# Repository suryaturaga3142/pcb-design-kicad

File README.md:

# pcb-design-kicad
Designing PCBs is an integral skill that takes you beyond breadboarding and using dev boards. It lets you combine different components with very little latency, and makes products look awesome!

Here's a collection of some of my favorite PCBs that I really enjoyed designing on my own. I don't just go and draw stuff up. I think of a use case first, like connecting devices to my laptop or using AUX cables for STM32. Then I go about employing the skills available to me.

## flash_adc1

My own design of a flash ADC that makes use of less digital combinationl logic and more buffering and chaining of comparators to directly obtain the converted reading. It's a unique design that saves on resources by leveraging a binary search style of output.

Typical ADCs are either SAR (Successive Approximation Register), Sigma-Delta, or Flash. SAR is resource efficient and used a lot to conserve area. Flash is extremely fast but resource heavy.

Performance wise, flash interests me a fair amount. It produces a thermometer code that is then converted to digital logic, but what if there was a better way? That long line of resistors always stood out to me. This is my design of a flash ADC based on binary search, where a cascade of logic allows you to directly collect the value.

## dsp1-stm32

A single PCB with an STM32H757 controller, specialized for signal processing. It has AUX plugs, buttons, switches, and potentiometers. There are also headers and sockets for timers, ADCs, SWD, UART, and I2C.

The PCB makes use of ADCs with internal OPAMPS, the DACs for the AUX output, jumpers for easy reconfiguration, and USB-C. It also allows the use of a dedicated 5V power supply as opposed to USB-C connection.

Designing this is proving to be quite challenging! Going about designing the circuit has taught me how to build protection circuits, read datasheets, calculate component values, determining appropriate footprints and routing patterns, and much more.

This isn't one of those projects that just "ends". This is one that I'm using to push the boundaries of my skills in PCB design. As I make progress in design, new ideas form, almost as if the PCB is creating itself! 

When I started, I added communication protocol pins, and then added on ADCs and DACs with AUX plugs. Then, I learnt how to manage power in PCBs and implemented better designs to route power and make use of noise filtering.

I then began working on the finer details like estimating capacitance values for circuits (like the HSE circuit) and implementing switching voltage regulators for lower voltage power supplies.

Then, I learnt of the importance of ESD protection for signals and the various types of protection for power lines and grounds.

Going about adding on more functionality like reverse polarity protection while ensuring all the design constraints are met is quite the challenge!

## usb-demux1

This was one of the first PCBs I've designed. I have only one USB-C receptacle on my laptop, so it's hard for me to connect multiple devices like microcontrollers and FPGAs without reconnecting each and every time.

This fixes my problem, lets me switch between different devices. Even better, it's got a USB-C plug so no more USB-C to A conversion!

## bluepill1-stm32

A small project just to get the hang of some routing and setting parameters based on a PCB printing agency.

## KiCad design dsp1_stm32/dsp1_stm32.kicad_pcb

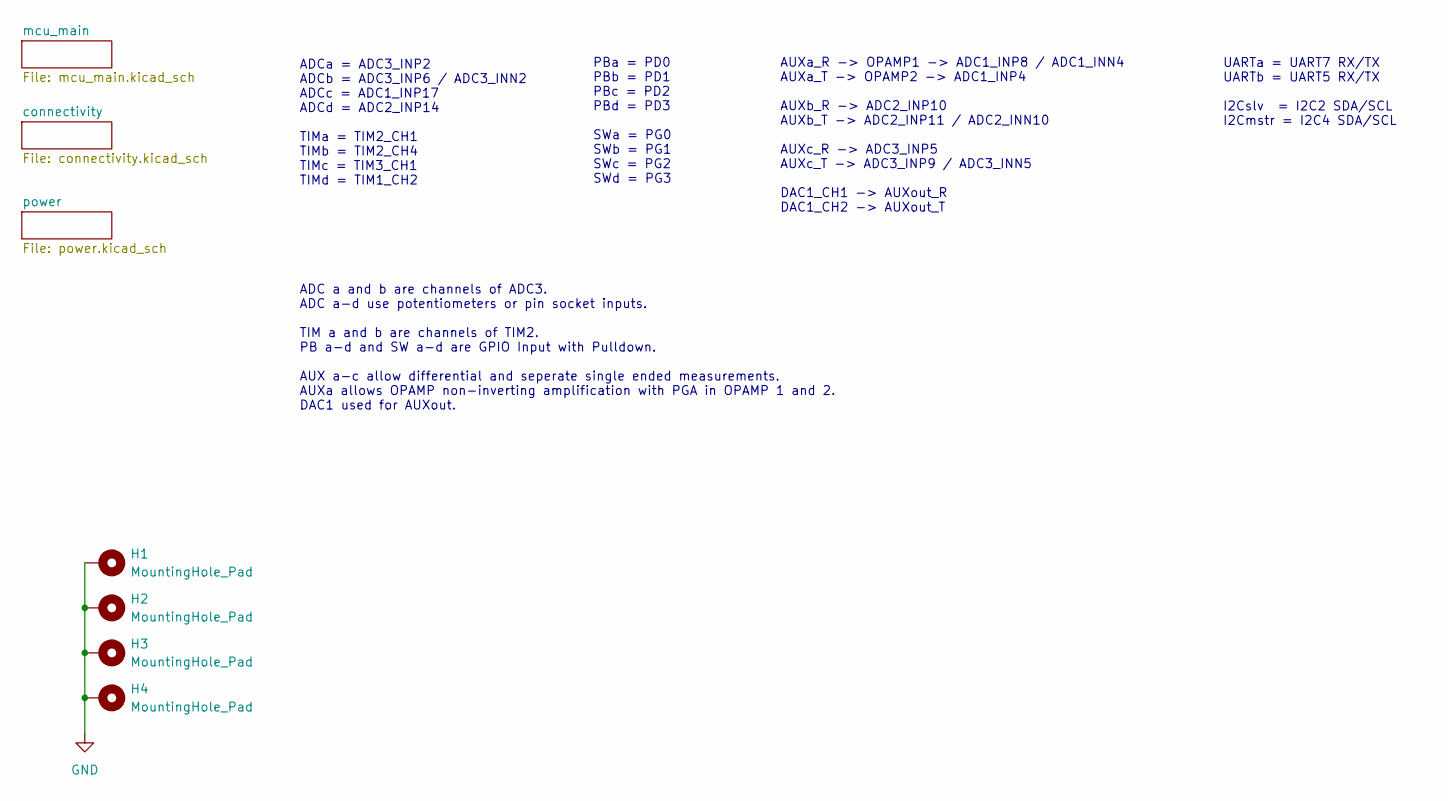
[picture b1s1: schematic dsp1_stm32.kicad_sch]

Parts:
H1, H2, H3, H4: MountingHole_Pad; MountingHole_2.2mm_M2_DIN965_Pad

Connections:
GND: H1.1, H2.1, H3.1, H4.1; also elsewhere on the board

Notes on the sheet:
PBa = PD0 PBb = PD1 PBc = PD2 PBd = PD3 SWa = PG0 SWb = PG1 SWc = PG2 SWd = PG3
ADCa = ADC3_INP2 ADCb = ADC3_INP6 / ADC3_INN2 ADCc = ADC1_INP17 ADCd = ADC2_INP14 TIMa = TIM2_CH1 TIMb = TIM2_CH4 TIMc = TIM3_CH1 TIMd = TIM1_CH2
ADC a and b are channels of ADC3. ADC a-d use potentiometers or pin socket inputs. TIM a and b are channels of TIM2. PB a-d and SW a-d are GPIO Input with Pulldown. AUX a-c allow differential and seperate single ended measurements. AUXa allows OPAMP non-inverting amplification with PGA in OPAMP 1 a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
UARTa = UART7 RX/TX UARTb = UART5 RX/TX I2Cslv = I2C2 SDA/SCL I2Cmstr = I2C4 SDA/SCL
AUXa_R -> OPAMP1 -> ADC1_INP8 / ADC1_INN4 AUXa_T -> OPAMP2 -> ADC1_INP4 AUXb_R -> ADC2_INP10 AUXb_T -> ADC2_INP11 / ADC2_INN10 AUXc_R -> ADC3_INP5 AUXc_T -> ADC3_INP9 / ADC3_INN5 DAC1_CH1 -> AUXout_R DAC1_CH2 -> AUXout_T

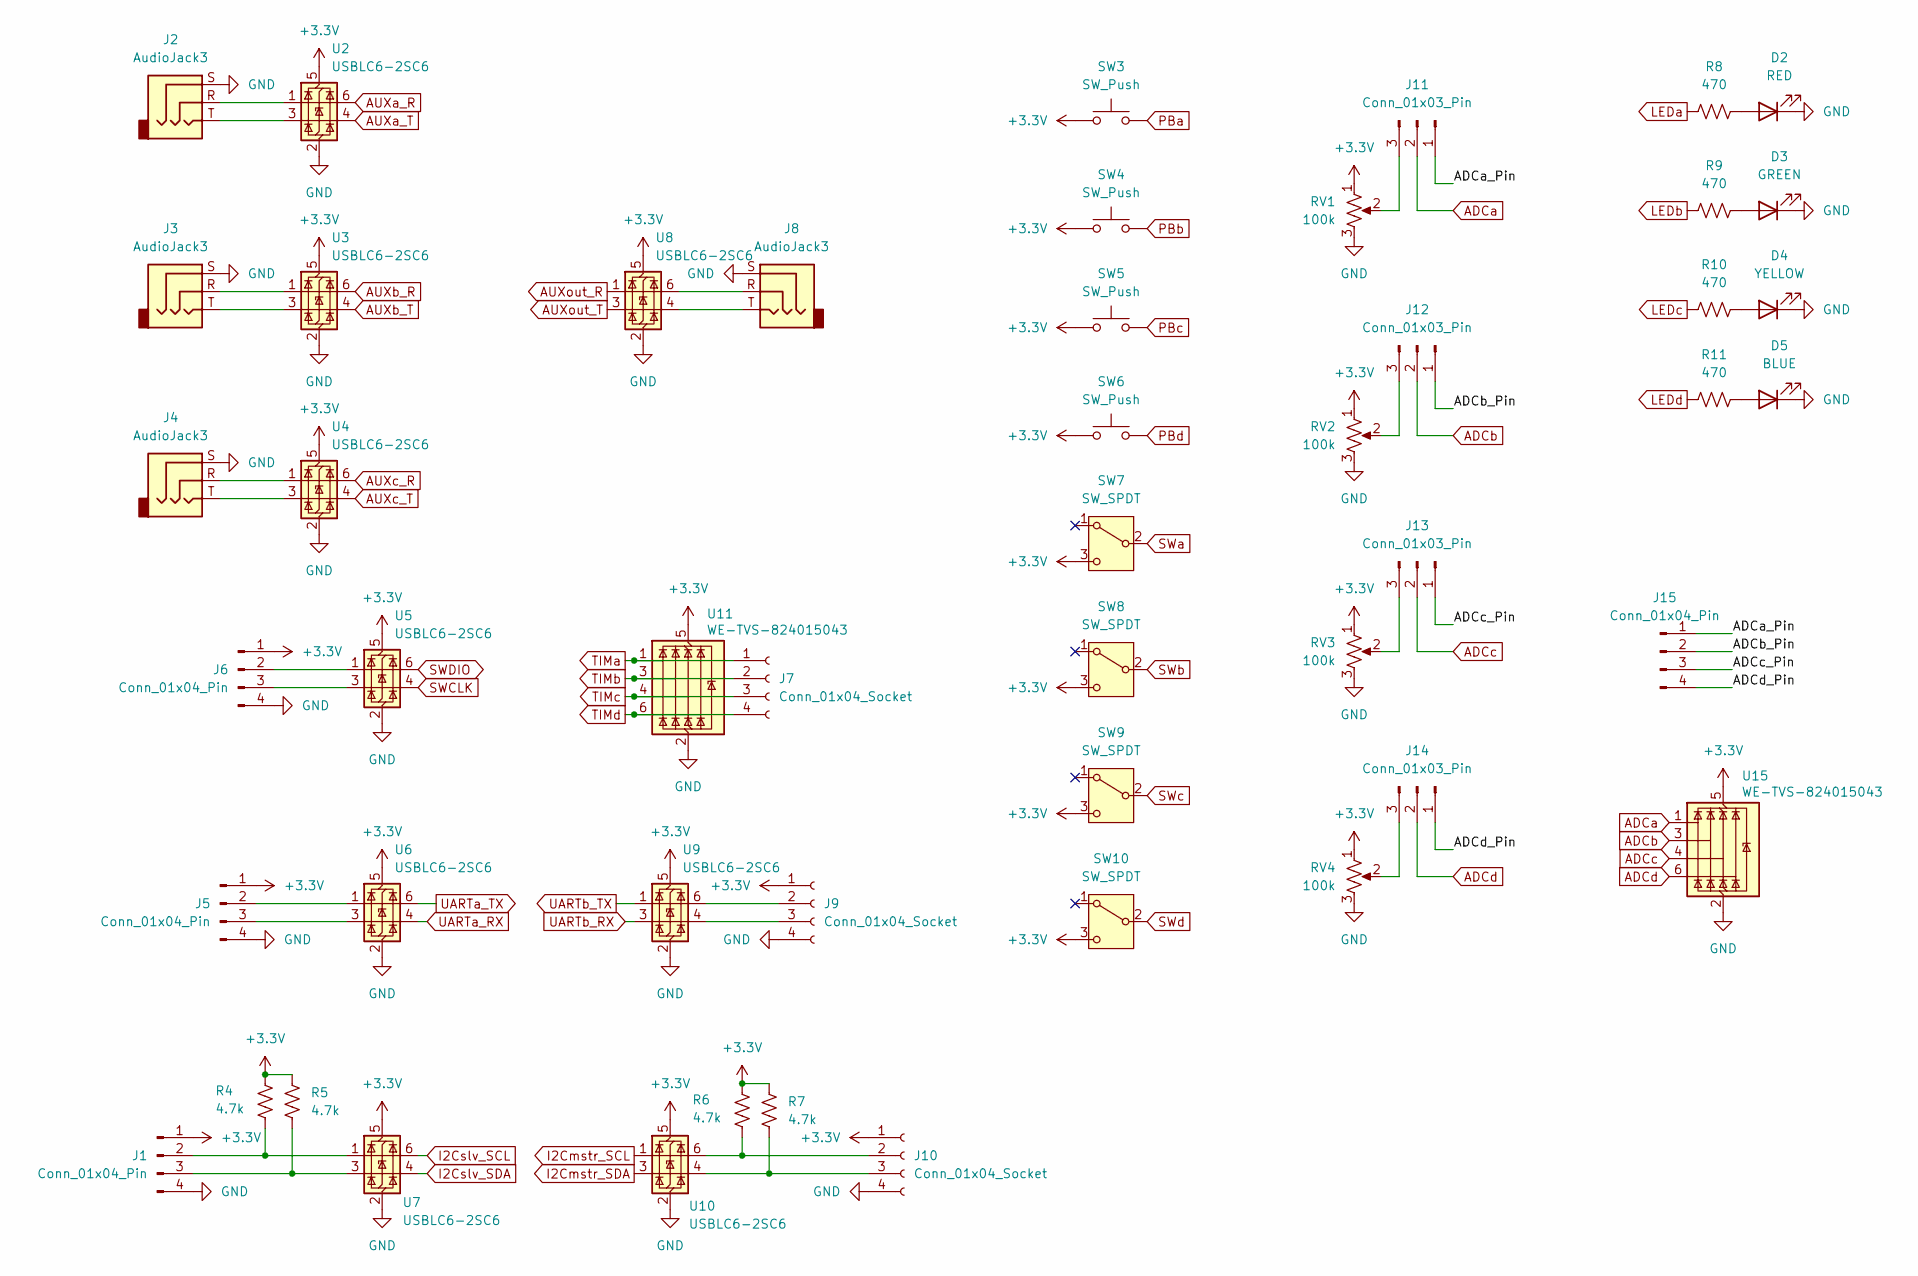
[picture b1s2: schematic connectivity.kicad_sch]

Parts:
D2: RED; LED_0805_2012Metric
D3: GREEN; LED_0805_2012Metric
D4: YELLOW; LED_0805_2012Metric
D5: BLUE; LED_0805_2012Metric
J1, J5, J6, J15: Conn_01x04_Pin; PinHeader_1x04_P2.54mm_Vertical
J2, J3, J4, J8: AudioJack3; Jack_3.5mm_CUI_SJ-3523-SMT_Horizontal
J7, J9, J10: Conn_01x04_Socket; PinSocket_1x04_P2.54mm_Vertical
J11, J12, J13, J14: Conn_01x03_Pin; PinHeader_1x03_P2.54mm_Vertical
R4, R5, R6, R7: 4.7k; R_0603_1608Metric
R8, R9, R10, R11: 470; R_0603_1608Metric
RV1, RV2, RV3, RV4: 100k; Potentiometer_ACP_CA6-H2,5_Horizontal
SW3, SW4, SW5, SW6: SW_Push; SW_SPST_PTS647_Sx38
SW7, SW8, SW9, SW10: SW_SPDT; SW_SPDT_PCM12
U2, U3, U4, U5, U6, U7, U8, U9, U10: USBLC6-2SC6; SOT-23-6
U11, U15: WE-TVS-824015043; SOT-23-6

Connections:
+3.3V: J1.1, J5.1, J6.1, J9.1, J10.1, R4.1, R5.1, R6.1, R7.1, RV1.1, RV2.1, RV3.1, RV4.1, SW3.1, SW4.1, SW5.1, SW6.1, SW7.3 (C), SW8.3 (C), SW9.3 (C), SW10.3 (C), U2.5 (VBUS), U3.5 (VBUS), U4.5 (VBUS), U5.5 (VBUS), U6.5 (VBUS), U7.5 (VBUS), U8.5 (VBUS), U9.5 (VBUS), U10.5 (VBUS), U11.5 (VBUS), U15.5 (VBUS); also elsewhere on the board
/connectivity/ADCa_Pin: J11.1, J15.1
/connectivity/ADCb_Pin: J12.1, J15.2
/connectivity/ADCc_Pin: J13.1, J15.3
/connectivity/ADCd_Pin: J14.1, J15.4
ADCa: J11.2, U15.1 (I/O1); also elsewhere on the board
ADCb: J12.2, U15.3 (I/O2); also elsewhere on the board
ADCc: J13.2, U15.4 (I/O3); also elsewhere on the board
ADCd: J14.2, U15.6 (I/O4); also elsewhere on the board
AUXa_R: U2.6 (I/O1); also elsewhere on the board
AUXa_T: U2.4 (I/O2); also elsewhere on the board
AUXb_R: U3.6 (I/O1); also elsewhere on the board
AUXb_T: U3.4 (I/O2); also elsewhere on the board
AUXc_R: U4.6 (I/O1); also elsewhere on the board
AUXc_T: U4.4 (I/O2); also elsewhere on the board
AUXout_R: U8.1 (I/O1); also elsewhere on the board
AUXout_T: U8.3 (I/O2); also elsewhere on the board
GND: D2.1 (K), D3.1 (K), D4.1 (K), D5.1 (K), J1.4, J2.S, J3.S, J4.S, J5.4, J6.4, J8.S, J9.4, J10.4, RV1.3, RV2.3, RV3.3, RV4.3, U2.2 (GND), U3.2 (GND), U4.2 (GND), U5.2 (GND), U6.2 (GND), U7.2 (GND), U8.2 (GND), U9.2 (GND), U10.2 (GND), U11.2 (GND), U15.2 (GND); also elsewhere on the board
I2Cmstr_SCL: U10.1 (I/O1); also elsewhere on the board
I2Cmstr_SDA: U10.3 (I/O2); also elsewhere on the board
I2Cslv_SCL: U7.6 (I/O1); also elsewhere on the board
I2Cslv_SDA: U7.4 (I/O2); also elsewhere on the board
LEDa: R8.1; also elsewhere on the board
LEDb: R9.1; also elsewhere on the board
LEDc: R10.1; also elsewhere on the board
LEDd: R11.1; also elsewhere on the board
unnamed: D2.2 (A), R8.2
unnamed: D3.2 (A), R9.2
unnamed: D4.2 (A), R10.2
unnamed: D5.2 (A), R11.2
unnamed: J1.2, R4.2, U7.1 (I/O1)
unnamed: J1.3, R5.2, U7.3 (I/O2)
unnamed: J2.R, U2.1 (I/O1)
unnamed: J2.T, U2.3 (I/O2)
unnamed: J3.R, U3.1 (I/O1)
unnamed: J3.T, U3.3 (I/O2)
unnamed: J4.R, U4.1 (I/O1)
unnamed: J4.T, U4.3 (I/O2)
unnamed: J5.2, U6.1 (I/O1)
unnamed: J5.3, U6.3 (I/O2)
unnamed: J6.2, U5.1 (I/O1)
unnamed: J6.3, U5.3 (I/O2)
unnamed: J8.R, U8.6 (I/O1)
unnamed: J8.T, U8.4 (I/O2)
unnamed: J9.2, U9.6 (I/O1)
unnamed: J9.3, U9.4 (I/O2)
unnamed: J10.2, R6.2, U10.6 (I/O1)
unnamed: J10.3, R7.2, U10.4 (I/O2)
unnamed: J11.3, RV1.2
unnamed: J12.3, RV2.2
unnamed: J13.3, RV3.2
unnamed: J14.3, RV4.2
PBa: SW3.2; also elsewhere on the board
PBb: SW4.2; also elsewhere on the board
PBc: SW5.2; also elsewhere on the board
PBd: SW6.2; also elsewhere on the board
SWCLK: U5.4 (I/O2); also elsewhere on the board
SWDIO: U5.6 (I/O1); also elsewhere on the board
SWa: SW7.2 (B); also elsewhere on the board
SWb: SW8.2 (B); also elsewhere on the board
SWc: SW9.2 (B); also elsewhere on the board
SWd: SW10.2 (B); also elsewhere on the board
TIMa: J7.1, U11.1 (I/O1); also elsewhere on the board
TIMb: J7.2, U11.3 (I/O2); also elsewhere on the board
TIMc: J7.3, U11.4 (I/O3); also elsewhere on the board
TIMd: J7.4, U11.6 (I/O4); also elsewhere on the board
UARTa_RX: U6.4 (I/O2); also elsewhere on the board
UARTa_TX: U6.6 (I/O1); also elsewhere on the board
UARTb_RX: U9.3 (I/O2); also elsewhere on the board
UARTb_TX: U9.1 (I/O1); also elsewhere on the board

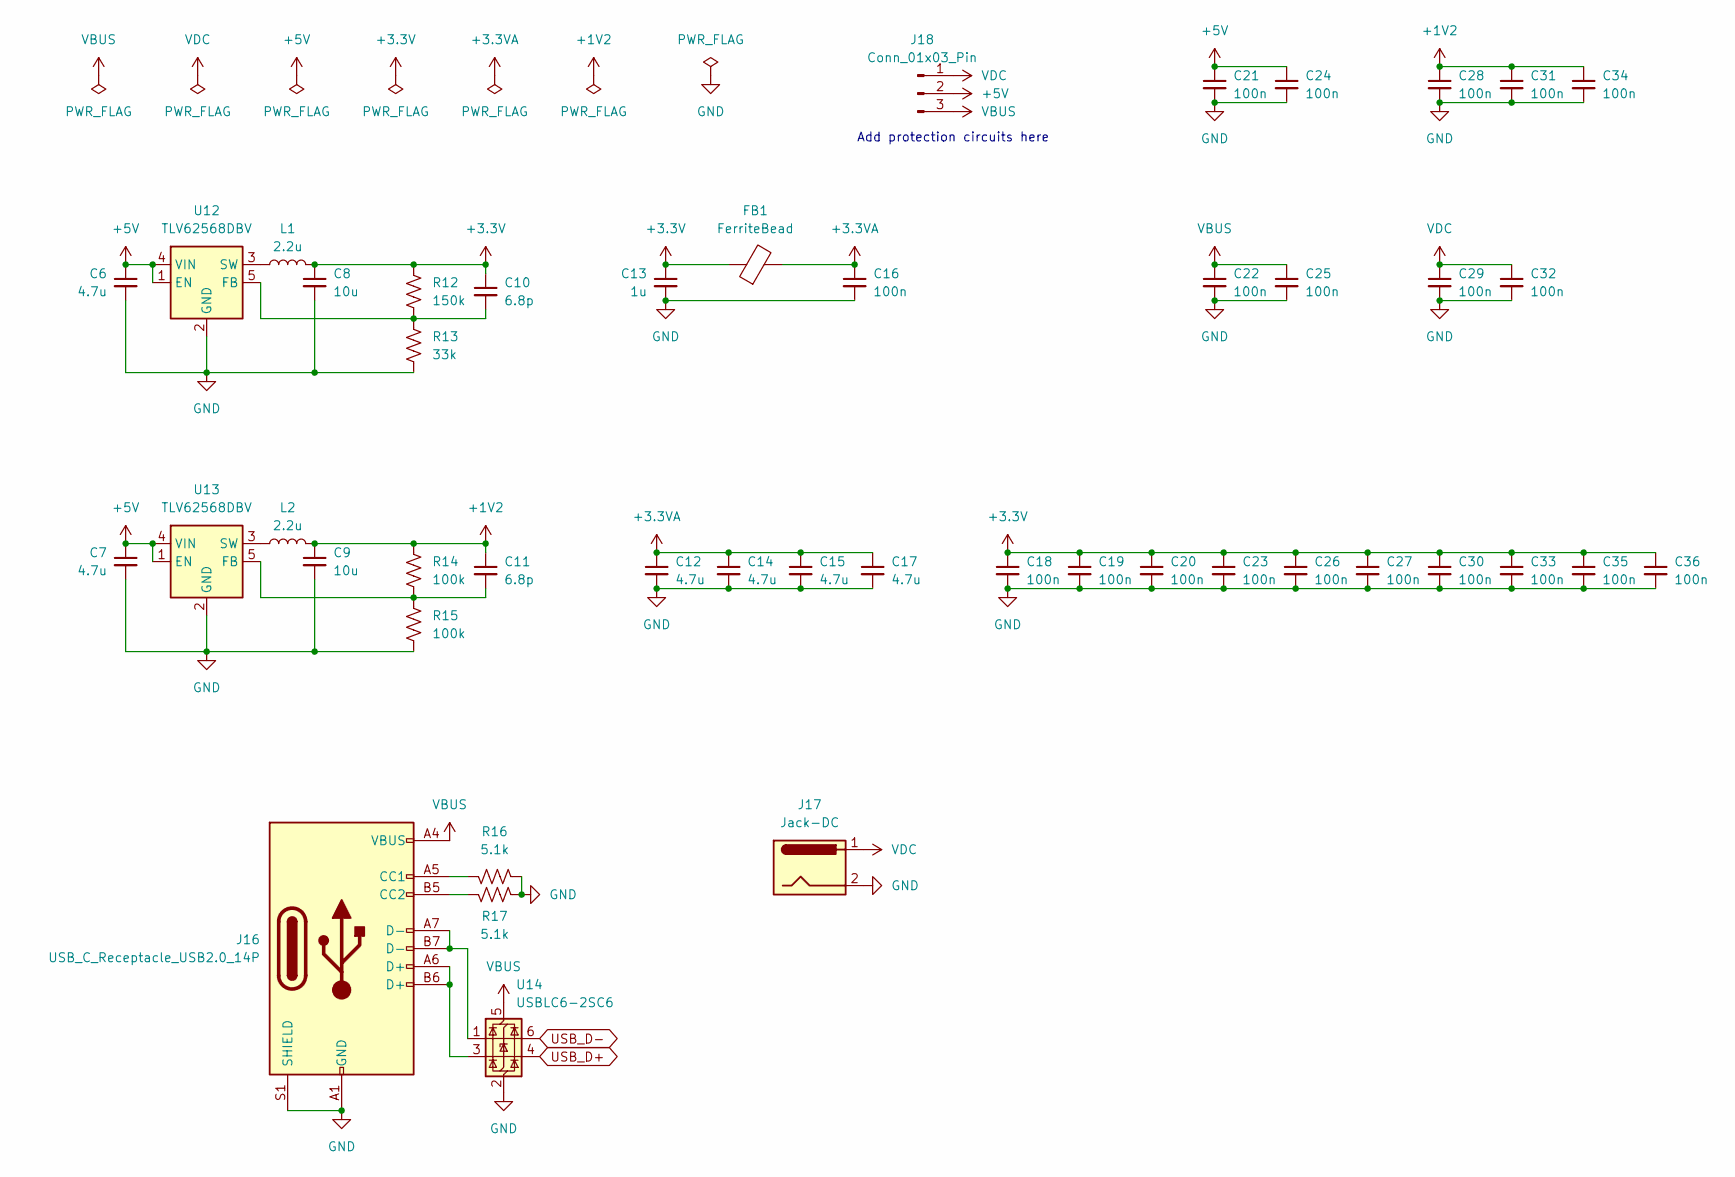
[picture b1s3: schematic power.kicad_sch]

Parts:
C6, C7, C12, C14, C15, C17: 4.7u; C_0603_1608Metric
C8, C9: 10u; C_0603_1608Metric
C10, C11: 6.8p; C_0603_1608Metric
C13: 1u; C_0603_1608Metric
C16, C18, C19, C20, C21, C22, C23, C24, C25, C26, C27, C28, C29, C30, C31, C32, C33, C34, C35, C36: 100n; C_0603_1608Metric
FB1: FerriteBead; L_0603_1608Metric
J16: USB_C_Receptacle_USB2.0_14P; USB_C_Receptacle_GCT_USB4105-xx-A_16P_TopMnt_Horizontal
J17: Jack-DC; BarrelJack_Horizontal
J18: Conn_01x03_Pin; PinHeader_1x03_P2.54mm_Vertical
L1, L2: 2.2u; L_0805_2012Metric
R12: 150k; R_0603_1608Metric
R13: 33k; R_0603_1608Metric
R14, R15: 100k; R_0603_1608Metric
R16, R17: 5.1k; R_0603_1608Metric
U12, U13: TLV62568DBV; SOT-23-5
U14: USBLC6-2SC6; SOT-23-6

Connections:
+1V2: C9.1, C11.1, C28.1, C31.1, C34.1, L2.2, R14.1; also elsewhere on the board
+3.3V: C8.1, C10.1, C13.1, C18.1, C19.1, C20.1, C23.1, C26.1, C27.1, C30.1, C33.1, C35.1, C36.1, FB1.1, L1.2, R12.1; also elsewhere on the board
+3.3VA: C12.1, C14.1, C15.1, C16.1, C17.1, FB1.2; also elsewhere on the board
+5V: C6.1, C7.1, C21.1, C24.1, J18.2, U12.1 (EN), U12.4 (VIN), U13.1 (EN), U13.4 (VIN); also elsewhere on the board
GND: C6.2, C7.2, C8.2, C9.2, C12.2, C13.2, C14.2, C15.2, C16.2, C17.2, C18.2, C19.2, C20.2, C21.2, C22.2, C23.2, C24.2, C25.2, C26.2, C27.2, C28.2, C29.2, C30.2, C31.2, C32.2, C33.2, C34.2, C35.2, C36.2, J16.A1 (GND), J16.A12 (GND), J16.B1 (GND), J16.B12 (GND), J16.S1 (SHIELD), J17.2, J17.3, R13.2, R15.2, R16.1, R17.1, U12.2 (GND), U13.2 (GND), U14.2 (GND); also elsewhere on the board
unnamed: J16.A5 (CC1), R16.2
unnamed: J16.B5 (CC2), R17.2
unnamed: J16.A6 (D+), J16.B6 (D+), U14.3 (I/O2)
unnamed: J16.A7 (D-), J16.B7 (D-), U14.1 (I/O1)
unnamed: C10.2, R12.2, R13.1, U12.5 (FB)
unnamed: L1.1, U12.3 (SW)
unnamed: C11.2, R14.2, R15.1, U13.5 (FB)
unnamed: L2.1, U13.3 (SW)
USB_D+: U14.4 (I/O2); also elsewhere on the board
USB_D-: U14.6 (I/O1); also elsewhere on the board
VBUS: C22.1, C25.1, J16.A4 (VBUS), J16.A9 (VBUS), J16.B4 (VBUS), J16.B9 (VBUS), J18.3, U14.5 (VBUS); also elsewhere on the board
VDC: C29.1, C32.1, J17.1, J18.1

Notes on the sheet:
Add protection circuits here

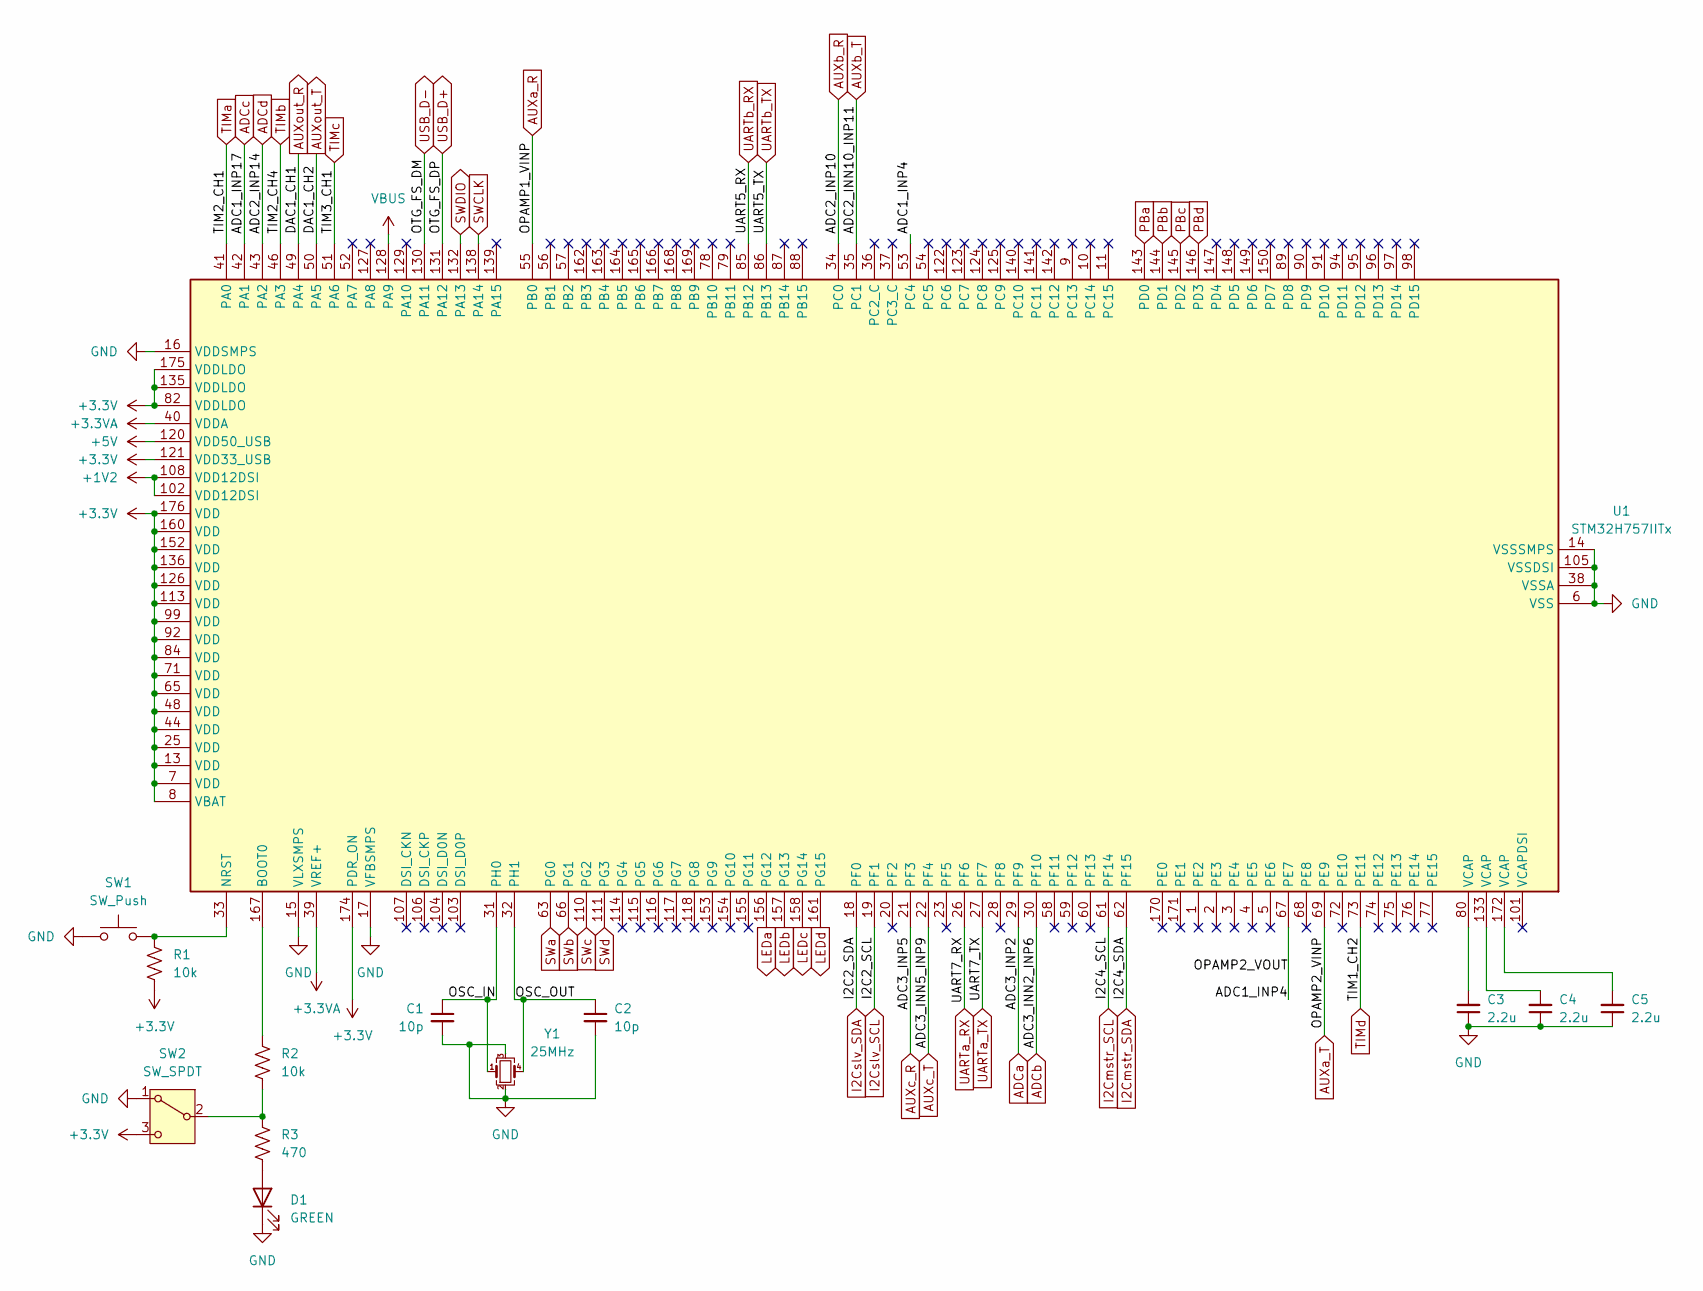
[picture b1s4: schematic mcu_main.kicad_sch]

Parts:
C1, C2: 10p; C_0402_1005Metric
C3, C4, C5: 2.2u; C_0603_1608Metric
D1: GREEN; LED_0805_2012Metric
R1, R2: 10k; R_0603_1608Metric
R3: 470; R_0603_1608Metric
SW1: SW_Push; SW_SPST_PTS647_Sx38
SW2: SW_SPDT; SW_SPDT_PCM12
U1: STM32H757IITx; LQFP-176_24x24mm_P0.5mm
Y1: 25MHz; Crystal_SMD_SeikoEpson_FA238-4Pin_3.2x2.5mm

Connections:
+1V2: U1.102 (VDD12DSI), U1.108 (VDD12DSI); also elsewhere on the board
+3.3V: R1.2, SW2.3 (C), U1.7 (VDD), U1.8 (VBAT), U1.13 (VDD), U1.25 (VDD), U1.44 (VDD), U1.48 (VDD), U1.65 (VDD), U1.71 (VDD), U1.82 (VDDLDO), U1.84 (VDD), U1.92 (VDD), U1.99 (VDD), U1.113 (VDD), U1.121 (VDD33_USB), U1.126 (VDD), U1.135 (VDDLDO), U1.136 (VDD), U1.152 (VDD), U1.160 (VDD), U1.174 (PDR_ON), U1.175 (VDDLDO), U1.176 (VDD); also elsewhere on the board
+3.3VA: U1.39 (VREF+), U1.40 (VDDA); also elsewhere on the board
+5V: U1.120 (VDD50_USB); also elsewhere on the board
/mcu_main/ADC1_INP4: U1.53 (PC4), U1.67 (PE7)
/mcu_main/OSC_IN: C1.1, U1.31 (PH0), Y1.1
/mcu_main/OSC_OUT: C2.1, U1.32 (PH1), Y1.4
ADCa: U1.29 (PF9); also elsewhere on the board
ADCb: U1.30 (PF10); also elsewhere on the board
ADCc: U1.42 (PA1); also elsewhere on the board
ADCd: U1.43 (PA2); also elsewhere on the board
AUXa_R: U1.55 (PB0); also elsewhere on the board
AUXa_T: U1.69 (PE9); also elsewhere on the board
AUXb_R: U1.34 (PC0); also elsewhere on the board
AUXb_T: U1.35 (PC1); also elsewhere on the board
AUXc_R: U1.21 (PF3); also elsewhere on the board
AUXc_T: U1.22 (PF4); also elsewhere on the board
AUXout_R: U1.49 (PA4); also elsewhere on the board
AUXout_T: U1.50 (PA5); also elsewhere on the board
GND: C1.2, C2.2, C3.1, C4.1, C5.1, D1.1 (K), SW1.1, SW2.1 (A), U1.6 (VSS), U1.12 (VSS), U1.14 (VSSSMPS), U1.15 (VLXSMPS), U1.16 (VDDSMPS), U1.17 (VFBSMPS), U1.24 (VSS), U1.38 (VSSA), U1.45 (VSS), U1.47 (VSS), U1.64 (VSS), U1.70 (VSS), U1.81 (VSS), U1.83 (VSS), U1.93 (VSS), U1.100 (VSS), U1.105 (VSSDSI), U1.109 (VSSDSI), U1.112 (VSS), U1.119 (VSS), U1.134 (VSS), U1.137 (VSS), U1.151 (VSS), U1.159 (VSS), U1.173 (VSS), Y1.2, Y1.3; also elsewhere on the board
I2Cmstr_SCL: U1.61 (PF14); also elsewhere on the board
I2Cmstr_SDA: U1.62 (PF15); also elsewhere on the board
I2Cslv_SCL: U1.19 (PF1); also elsewhere on the board
I2Cslv_SDA: U1.18 (PF0); also elsewhere on the board
LEDa: U1.156 (PG12); also elsewhere on the board
LEDb: U1.157 (PG13); also elsewhere on the board
LEDc: U1.158 (PG14); also elsewhere on the board
LEDd: U1.161 (PG15); also elsewhere on the board
unnamed: C3.2, U1.80 (VCAP)
unnamed: C4.2, U1.133 (VCAP)
unnamed: C5.2, U1.172 (VCAP)
unnamed: D1.2 (A), R3.2
unnamed: R2.1, R3.1, SW2.2 (B)
unnamed: R2.2, U1.167 (BOOT0)
unnamed: R1.1, SW1.2, U1.33 (NRST)
PBa: U1.143 (PD0); also elsewhere on the board
PBb: U1.144 (PD1); also elsewhere on the board
PBc: U1.145 (PD2); also elsewhere on the board
PBd: U1.146 (PD3); also elsewhere on the board
SWCLK: U1.138 (PA14); also elsewhere on the board
SWDIO: U1.132 (PA13); also elsewhere on the board
SWa: U1.63 (PG0); also elsewhere on the board
SWb: U1.66 (PG1); also elsewhere on the board
SWc: U1.110 (PG2); also elsewhere on the board
SWd: U1.111 (PG3); also elsewhere on the board
TIMa: U1.41 (PA0); also elsewhere on the board
TIMb: U1.46 (PA3); also elsewhere on the board
TIMc: U1.51 (PA6); also elsewhere on the board
TIMd: U1.73 (PE11); also elsewhere on the board
UARTa_RX: U1.26 (PF6); also elsewhere on the board
UARTa_TX: U1.27 (PF7); also elsewhere on the board
UARTb_RX: U1.85 (PB12); also elsewhere on the board
UARTb_TX: U1.86 (PB13); also elsewhere on the board
USB_D+: U1.131 (PA12); also elsewhere on the board
USB_D-: U1.130 (PA11); also elsewhere on the board
VBUS: U1.128 (PA9); also elsewhere on the board

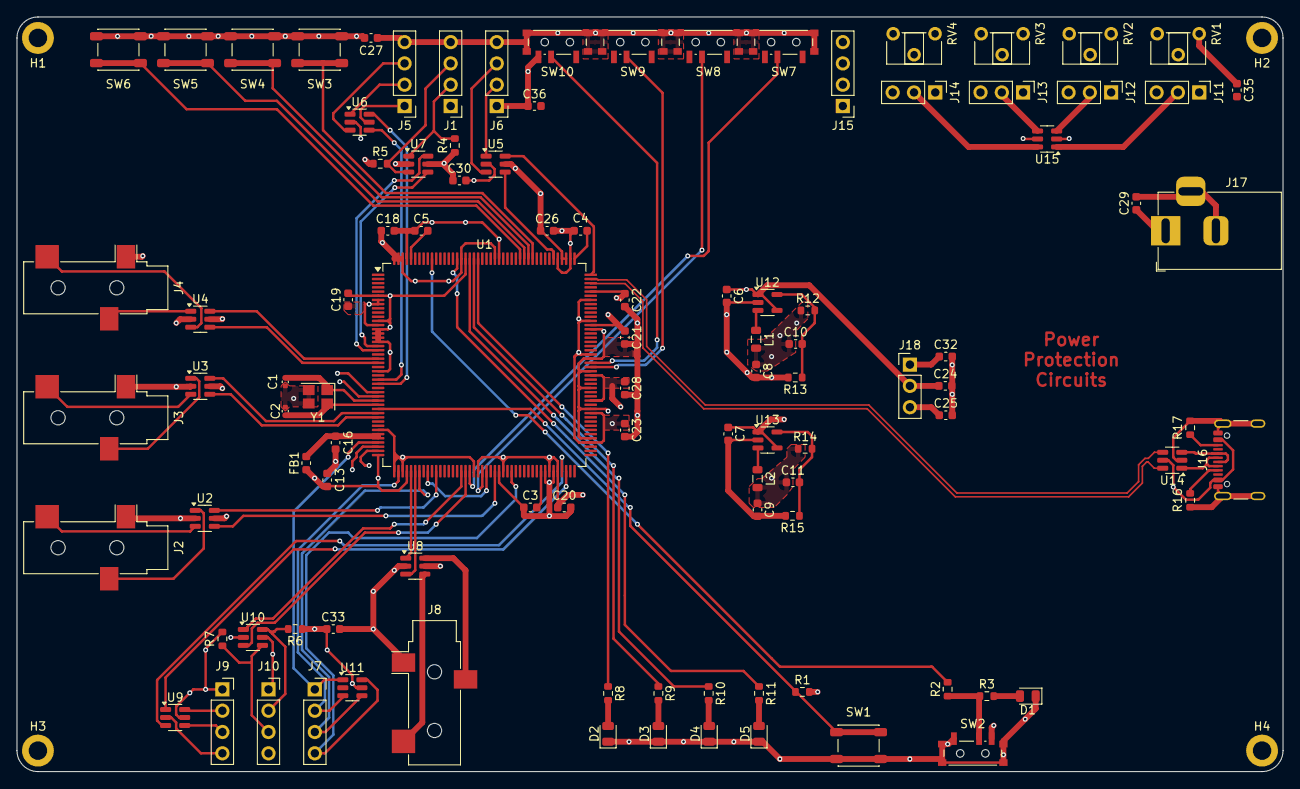
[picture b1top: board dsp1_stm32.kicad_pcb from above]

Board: 4 copper layers, 151.0 x 90.0 mm, 107 parts (0 on the bottom side), 95 nets.

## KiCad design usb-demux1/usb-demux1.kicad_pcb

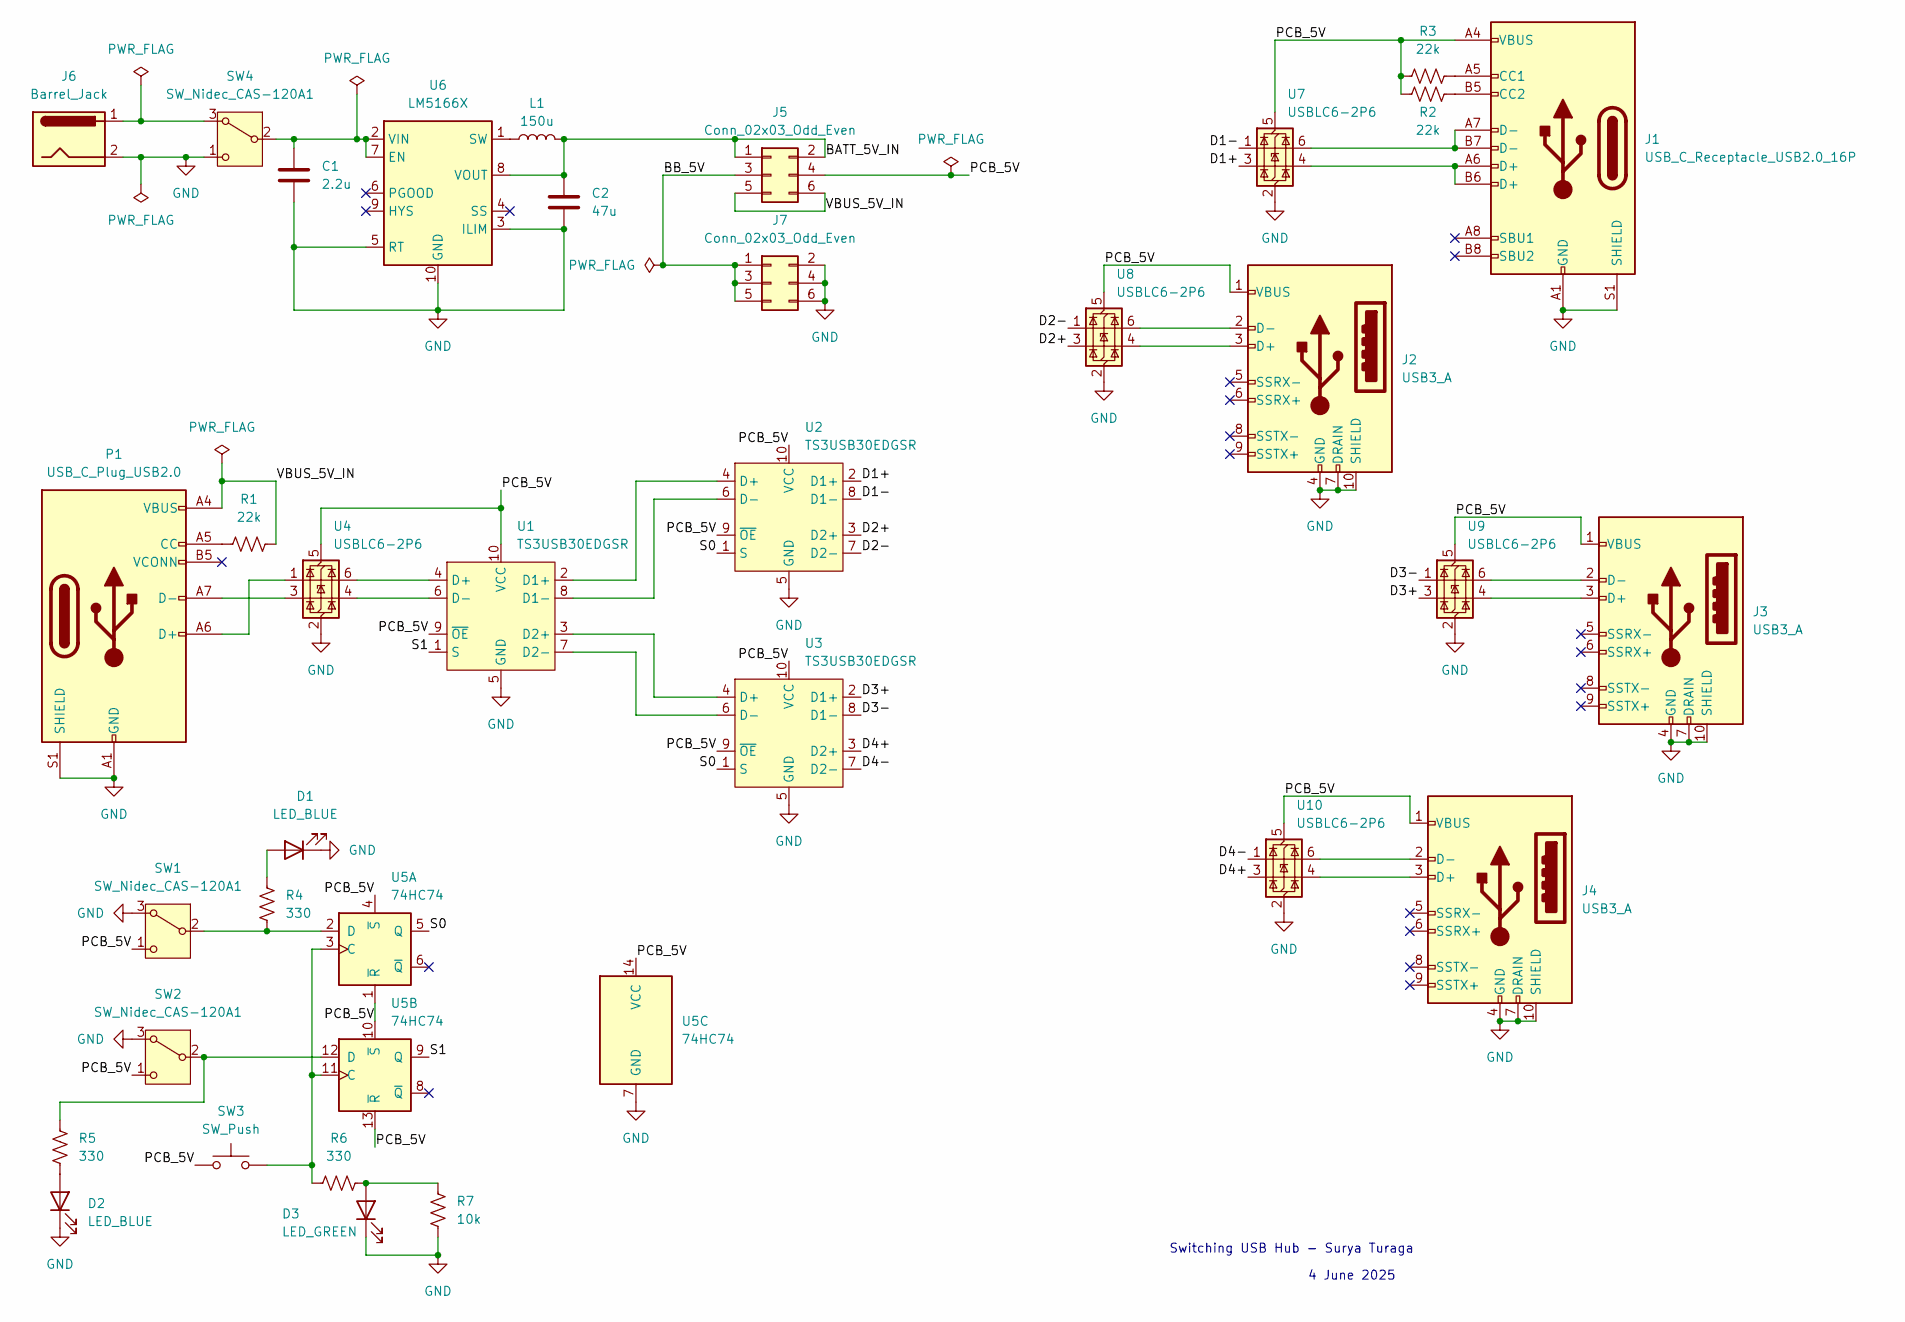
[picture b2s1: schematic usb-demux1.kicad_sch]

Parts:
C1: 2.2u; C_0805_2012Metric
C2: 47u; C_0805_2012Metric
D1, D2: LED_BLUE; LED_0805_2012Metric
D3: LED_GREEN; LED_0805_2012Metric
J1: USB_C_Receptacle_USB2.0_16P; USB_C_Receptacle_Molex_105450-0101
J2, J3, J4: USB3_A; USB3_A_Receptacle_Wuerth_692122030100
J5, J7: Conn_02x03_Odd_Even; PinHeader_2x03_P2.54mm_Vertical
J6: Barrel_Jack; BarrelJack_Horizontal
L1: 150u; L_0805_2012Metric
P1: USB_C_Plug_USB2.0; USB_C_Plug_Molex_105444
R1, R2, R3: 22k; R_0805_2012Metric
R4, R5, R6: 330; R_0805_2012Metric
R7: 10k; R_0805_2012Metric
SW1, SW2, SW4: SW_Nidec_CAS-120A1; Nidec_Copal_CAS-120A
SW3: SW_Push; SW_SPST_PTS645
U1, U2, U3: TS3USB30EDGSR; VSSOP-10_3x3mm_P0.5mm
U4, U7, U8, U9, U10: USBLC6-2P6; SOT-666
U5: 74HC74; DIP-14_W7.62mm_SMDSocket_SmallPads
U6: LM5166X; Texas_S-PVSON-N10_ThermalVias

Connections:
/BATT_5V_IN: C2.1, J5.1, J5.2, L1.2, U6.8 (VOUT)
/BB_5V: J5.3, J7.1, J7.3, J7.5
/D1+: U2.2 (D1+), U7.3 (I/O2)
/D1-: U2.8 (D1-), U7.1 (I/O1)
/D2+: U2.3 (D2+), U8.3 (I/O2)
/D2-: U2.7 (D2-), U8.1 (I/O1)
/D3+: U3.2 (D1+), U9.3 (I/O2)
/D3-: U3.8 (D1-), U9.1 (I/O1)
/D4+: U3.3 (D2+), U10.3 (I/O2)
/D4-: U3.7 (D2-), U10.1 (I/O1)
/PCB_5V: J1.A4 (VBUS), J1.A9 (VBUS), J1.B4 (VBUS), J1.B9 (VBUS), J2.1 (VBUS), J3.1 (VBUS), J4.1 (VBUS), J5.4, R2.1, R3.1, SW1.1 (C), SW2.1 (C), SW3.1, U1.9 (~OE), U1.10 (VCC), U2.9 (~OE), U2.10 (VCC), U3.9 (~OE), U3.10 (VCC), U4.5 (VBUS), U5.1 (~R), U5.4 (~S), U5.10 (~S), U5.13 (~R), U5.14 (VCC), U7.5 (VBUS), U8.5 (VBUS), U9.5 (VBUS), U10.5 (VBUS)
/S0: U2.1 (S), U3.1 (S), U5.5 (Q)
/S1: U1.1 (S), U5.9 (Q)
/VBUS_5V_IN: J5.5, J5.6, P1.A4 (VBUS), P1.A9 (VBUS), P1.B4 (VBUS), P1.B9 (VBUS), R1.2
GND: C1.2, C2.2, D1.1 (K), D2.1 (K), D3.1 (K), J1.A1 (GND), J1.A12 (GND), J1.B1 (GND), J1.B12 (GND), J1.S1 (SHIELD), J2.4 (GND), J2.7 (DRAIN), J2.10 (SHIELD), J3.4 (GND), J3.7 (DRAIN), J3.10 (SHIELD), J4.4 (GND), J4.7 (DRAIN), J4.10 (SHIELD), J6.2, J7.2, J7.4, J7.6, P1.A1 (GND), P1.A12 (GND), P1.B1 (GND), P1.B12 (GND), P1.S1 (SHIELD), R7.2, SW1.3 (A), SW2.3 (A), SW4.1 (C), U1.5 (GND), U2.5 (GND), U3.5 (GND), U4.2 (GND), U5.7 (GND), U6.3 (ILIM), U6.5 (RT), U6.10 (GND), U6.11 (GND), U7.2 (GND), U8.2 (GND), U9.2 (GND), U10.2 (GND)
unnamed: D1.2 (A), R4.1
unnamed: D2.2 (A), R5.1
unnamed: D3.2 (A), R6.2, R7.1
unnamed: J1.A5 (CC1), R3.2
unnamed: J1.B5 (CC2), R2.2
unnamed: J1.A6 (D+), J1.B6 (D+), U7.4 (I/O2)
unnamed: J1.A7 (D-), J1.B7 (D-), U7.6 (I/O1)
unnamed: J2.3 (D+), U8.4 (I/O2)
unnamed: J2.2 (D-), U8.6 (I/O1)
unnamed: J3.3 (D+), U9.4 (I/O2)
unnamed: J3.2 (D-), U9.6 (I/O1)
unnamed: J4.3 (D+), U10.4 (I/O2)
unnamed: J4.2 (D-), U10.6 (I/O1)
unnamed: P1.A5 (CC), R1.1
unnamed: P1.A6 (D+), U4.1 (I/O1)
unnamed: P1.A7 (D-), U4.3 (I/O2)
unnamed: R4.2, SW1.2 (B), U5.2 (D)
unnamed: R5.2, SW2.2 (B), U5.12 (D)
unnamed: J6.1, SW4.3 (A)
unnamed: C1.1, SW4.2 (B), U6.2 (VIN), U6.7 (EN)
unnamed: U1.2 (D1+), U2.4 (D+)
unnamed: U1.8 (D1-), U2.6 (D-)
unnamed: U1.3 (D2+), U3.4 (D+)
unnamed: U1.7 (D2-), U3.6 (D-)
unnamed: U1.4 (D+), U4.6 (I/O1)
unnamed: U1.6 (D-), U4.4 (I/O2)
unnamed: R6.1, SW3.2, U5.3 (C), U5.11 (C)
unnamed: L1.1, U6.1 (SW)

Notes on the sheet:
4 June 2025
Switching USB Hub - Surya Turaga

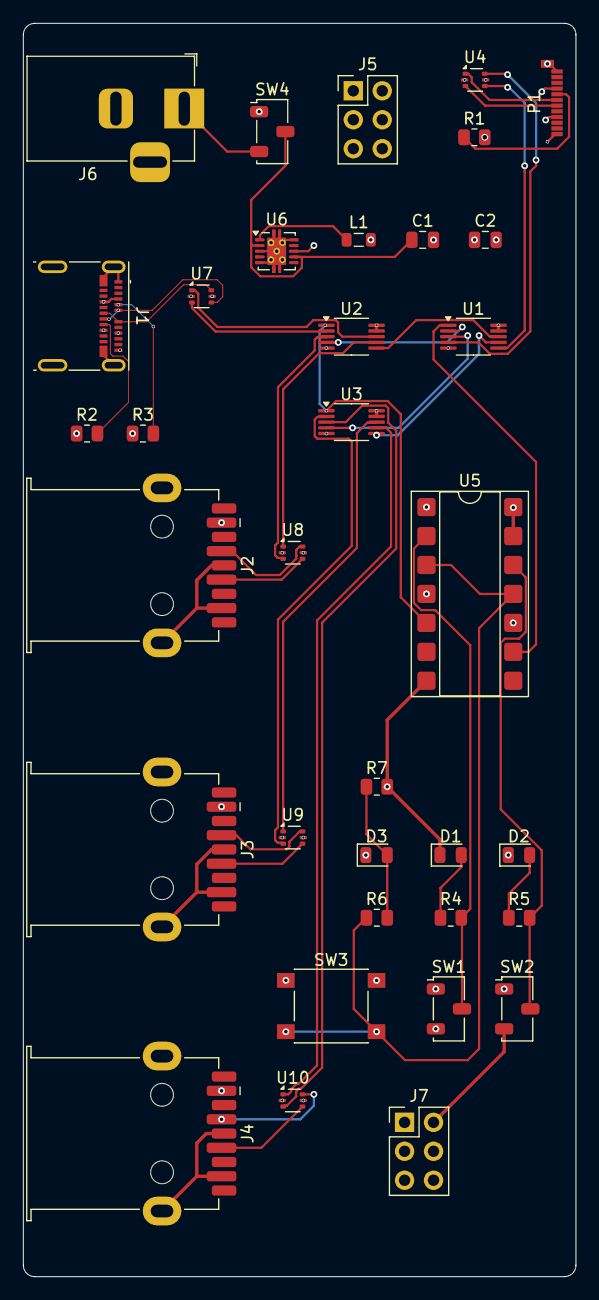
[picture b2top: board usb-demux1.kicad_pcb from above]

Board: 4 copper layers, 48.5 x 110.0 mm, 35 parts (0 on the bottom side), 43 nets.
